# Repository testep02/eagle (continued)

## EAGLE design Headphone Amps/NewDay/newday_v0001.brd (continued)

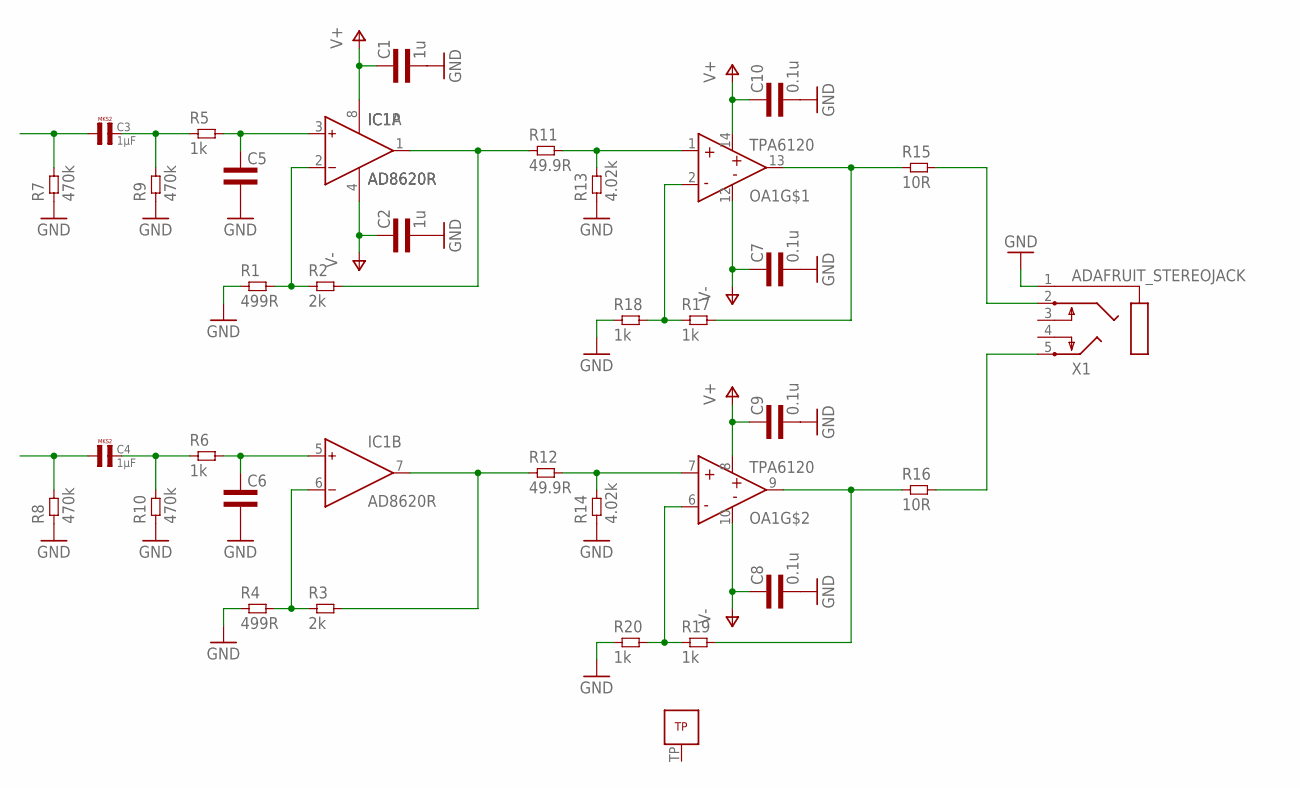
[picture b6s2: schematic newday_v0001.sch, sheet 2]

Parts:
C1, C2: 1u; 0805L3
C3, C4: 1µF; R5B3K5
C5, C6: CAP0603L3; 0603L3
C7, C8: 0.1u; 0603L3
C9, C10: 0.1u; 0805L3
IC1: AD8620R; SO8
OA1: TPA6120QFN; S-PVQFN-N14
R1, R4: 499R; 0603L3
R2, R3: 2k; 0603L3
R5, R6, R17, R18, R19, R20: 1k; 0603L3
R7, R8, R9, R10: 470k; 0603L3
R11, R12: 49.9R; 0805L3
R13, R14: 4.02k; 0805L3
R15, R16: 10R; 1210L3
X1: ADAFRUIT_STEREOJACK; ADAFRUIT_STX3100

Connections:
GND: C1.2, C2.2, C5.P$2 (2), C6.P$2 (2), C7.P$2 (2), C8.P$2 (2), C9.2, C10.2, R1.P$1 (1), R4.P$1 (1), R7.P$1 (1), R8.P$1 (1), R9.P$1 (1), R10.P$1 (1), R13.1, R14.1, R18.P$1 (1), R20.P$1 (1), X1.1; also elsewhere on the board
LEFT_BUF_FB: OA1.2 (IN-), R17.P$1 (1), R18.P$2 (2)
LEFT_BUF_IN: OA1.1 (IN+), R11.2, R13.2
LEFT_BUF_OUT: OA1.13 (OUT), R15.P$1 (1), R17.P$2 (2)
LEFT_CAP_OUT: C3.2, R5.P$1 (1), R9.P$2 (2)
LEFT_FILTER_OUT: C5.P$1 (1), IC1.3 (IN+), R5.P$2 (2)
LEFT_GAIN_FB: IC1.2 (IN-), R1.P$2 (2), R2.P$1 (1)
LEFT_GAIN_OUT: IC1.1 (OUT), R2.P$2 (2), R11.1
LEFT_HP_OUT: R15.P$2 (2), X1.2
LEFT_IN: C3.1, R7.P$2 (2)
RIGHT_BUF_FB: OA1.6 (IN-), R19.P$1 (1), R20.P$2 (2)
RIGHT_BUF_IN: OA1.7 (IN+), R12.2, R14.2
RIGHT_BUF_OUT: OA1.9 (OUT), R16.P$1 (1), R19.P$2 (2)
RIGHT_CAP_OUT: C4.2, R6.P$1 (1), R10.P$2 (2)
RIGHT_FILTER_OUT: C6.P$1 (1), IC1.5 (IN+), R6.P$2 (2)
RIGHT_GAIN_FB: IC1.6 (IN-), R3.P$1 (1), R4.P$2 (2)
RIGHT_GAIN_OUT: IC1.7 (OUT), R3.P$2 (2), R12.1
RIGHT_HP_OUT: R16.P$2 (2), X1.5
RIGHT_IN: C4.1, R8.P$2 (2)
V+: C1.1, C9.1, C10.1, IC1.8 (V+), OA1.8 (V+), OA1.14 (V+); also elsewhere on the board
V-: C2.1, C7.P$1 (1), C8.P$1 (1), IC1.4 (V-), OA1.10 (V-), OA1.12 (V-); also elsewhere on the board

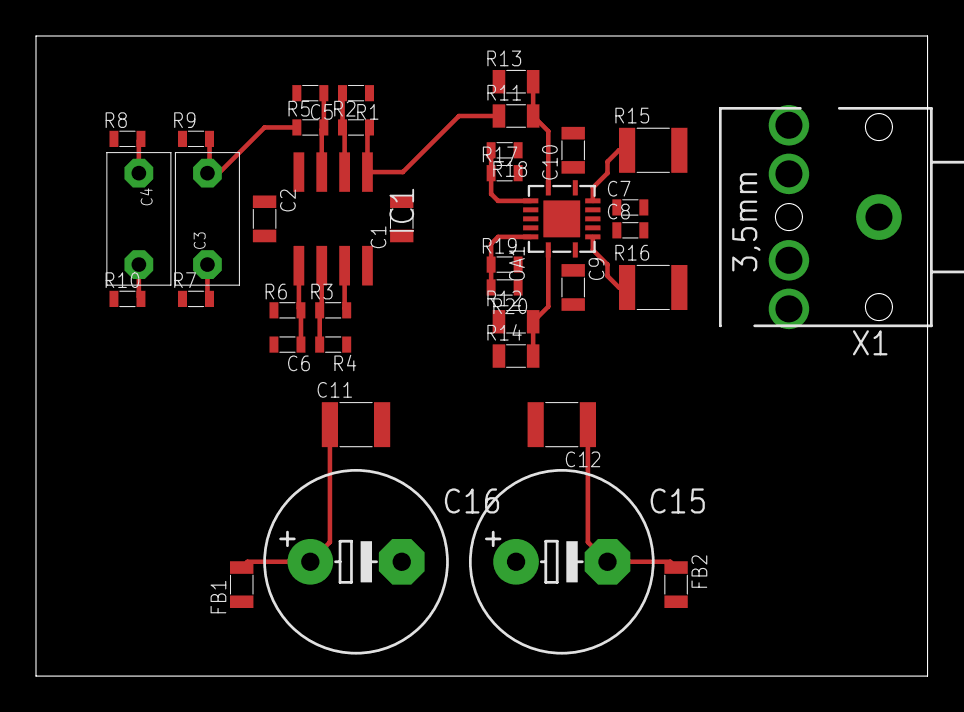
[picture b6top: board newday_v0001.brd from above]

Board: 2 copper layers, 49.5 x 35.6 mm, 39 parts (0 on the bottom side), 21 nets.

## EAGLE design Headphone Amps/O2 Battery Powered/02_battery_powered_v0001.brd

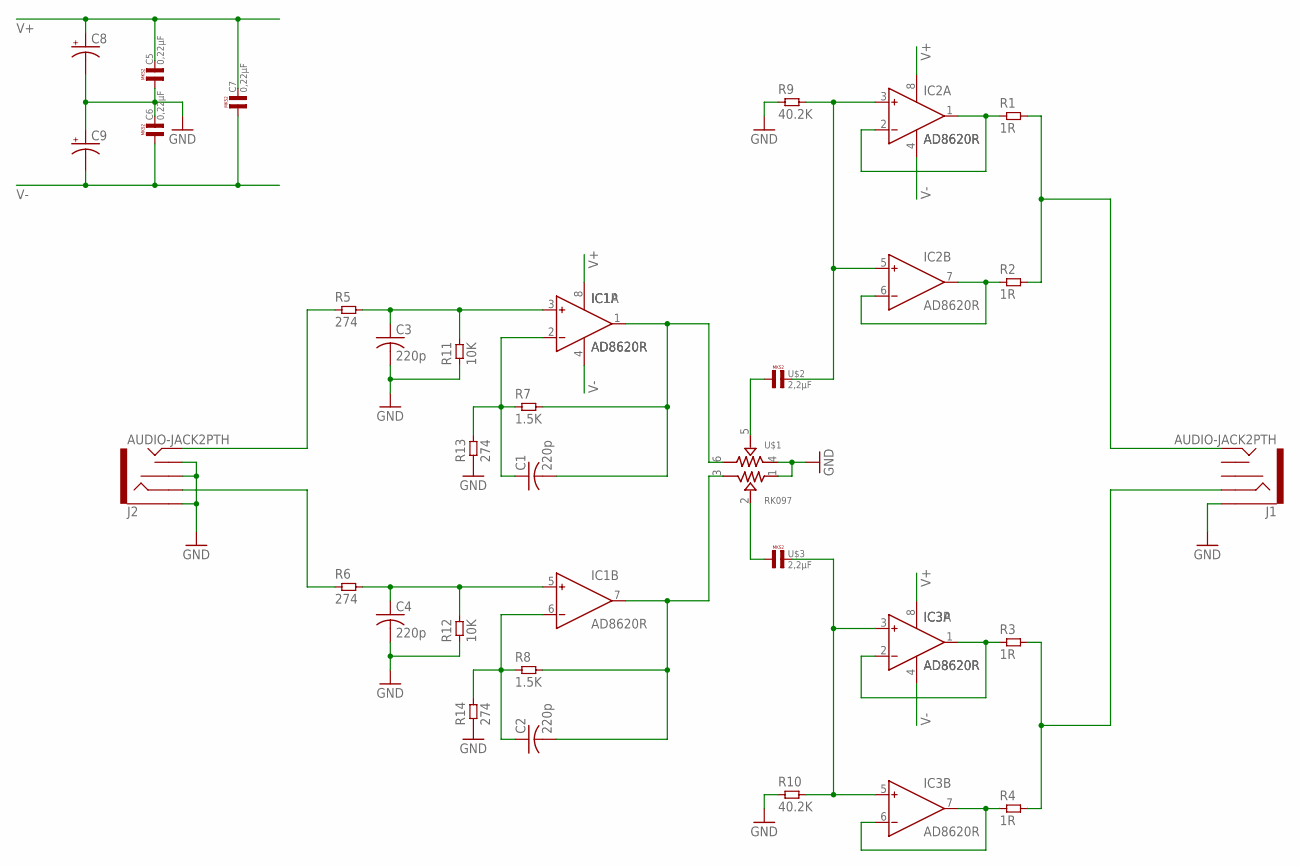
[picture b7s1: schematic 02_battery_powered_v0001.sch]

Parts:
C1, C2, C3, C4: 220p; C025-050X050
C5, C6, C7: 0,22µF; R5B3
C8, C9: CPOL-US150CLZ-1010; 150CLZ-1010
IC1, IC2, IC3: AD8620R; SO8
J1, J2: AUDIO-JACK2PTH; AUDIO-JACK
R1, R2, R3, R4: 1R; 1206L3
R5, R6, R13, R14: 274; 0603L3
R7, R8: 1.5K; 0603L3
R9, R10: 40.2K; 0603L3
R11, R12: 10K; 0603L3
U$1: RK097
U$2, U$3: 2,2µF; R5B7K2

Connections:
GND: C3.2, C4.2, C5.1, C6.2, C8.-, C9.+, J1.SLEEVE, J2.RSH, J2.SLEEVE, J2.TSH, R9.P$1 (1), R10.P$1 (1), R11.P$1 (1), R12.P$1 (1), R13.P$1 (1), R14.P$1 (1), U$1.1, U$1.4
unnamed: IC2.1 (OUT), IC2.2 (IN-), R1.1
unnamed: IC2.6 (IN-), IC2.7 (OUT), R2.1
unnamed: J1.TIP, R1.2, R2.2
unnamed: IC3.1 (OUT), IC3.2 (IN-), R3.1
unnamed: IC3.6 (IN-), IC3.7 (OUT), R4.1
unnamed: J1.RING, R3.2, R4.2
unnamed: C3.1, IC1.3 (IN+), R5.P$2 (2), R11.P$2 (2)
unnamed: C4.1, IC1.5 (IN+), R6.P$2 (2), R12.P$2 (2)
unnamed: C1.2, IC1.1 (OUT), R7.P$2 (2), U$1.6
unnamed: C2.2, IC1.7 (OUT), R8.P$2 (2), U$1.3
unnamed: C1.1, IC1.2 (IN-), R7.P$1 (1), R13.P$2 (2)
unnamed: C2.1, IC1.6 (IN-), R8.P$1 (1), R14.P$2 (2)
unnamed: U$1.5, U$2.1
unnamed: U$1.2, U$3.1
unnamed: IC2.3 (IN+), IC2.5 (IN+), R9.P$2 (2), U$2.2
unnamed: IC3.3 (IN+), IC3.5 (IN+), R10.P$2 (2), U$3.2
unnamed: J2.TIP, R5.P$1 (1)
unnamed: J2.RING, R6.P$1 (1)
V+: C5.2, C7.2, C8.+, IC1.8 (V+), IC2.8 (V+), IC3.8 (V+)
V-: C6.1, C7.1, C9.-, IC1.4 (V-), IC2.4 (V-), IC3.4 (V-)

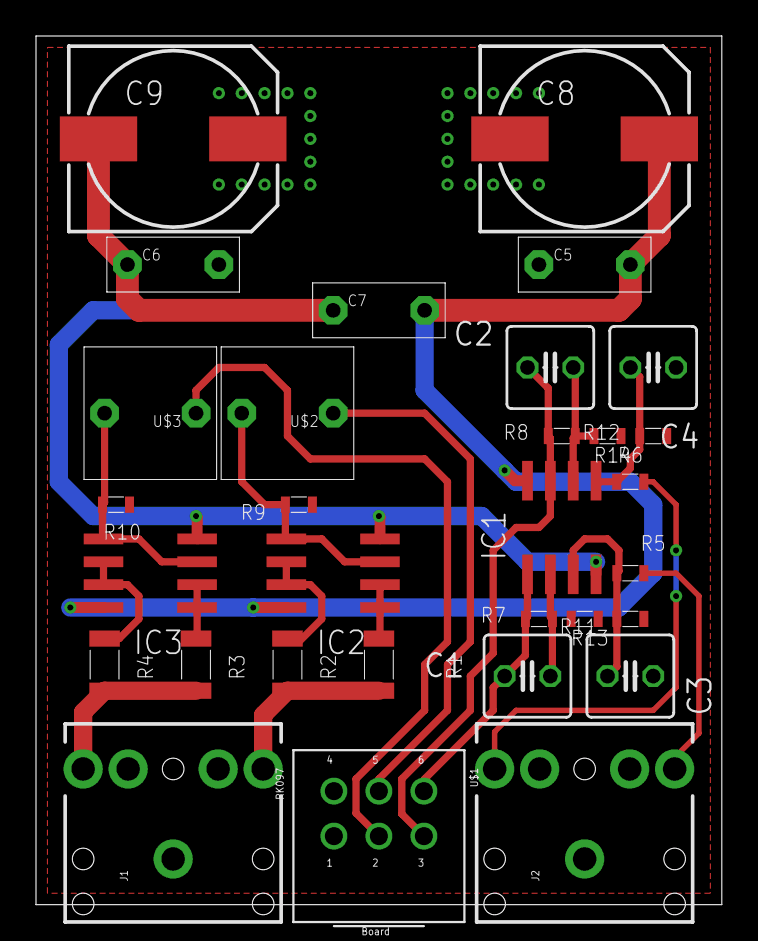
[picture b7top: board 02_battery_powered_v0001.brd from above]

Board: 2 copper layers, 38.1 x 48.3 mm, 31 parts (0 on the bottom side), 21 nets.
